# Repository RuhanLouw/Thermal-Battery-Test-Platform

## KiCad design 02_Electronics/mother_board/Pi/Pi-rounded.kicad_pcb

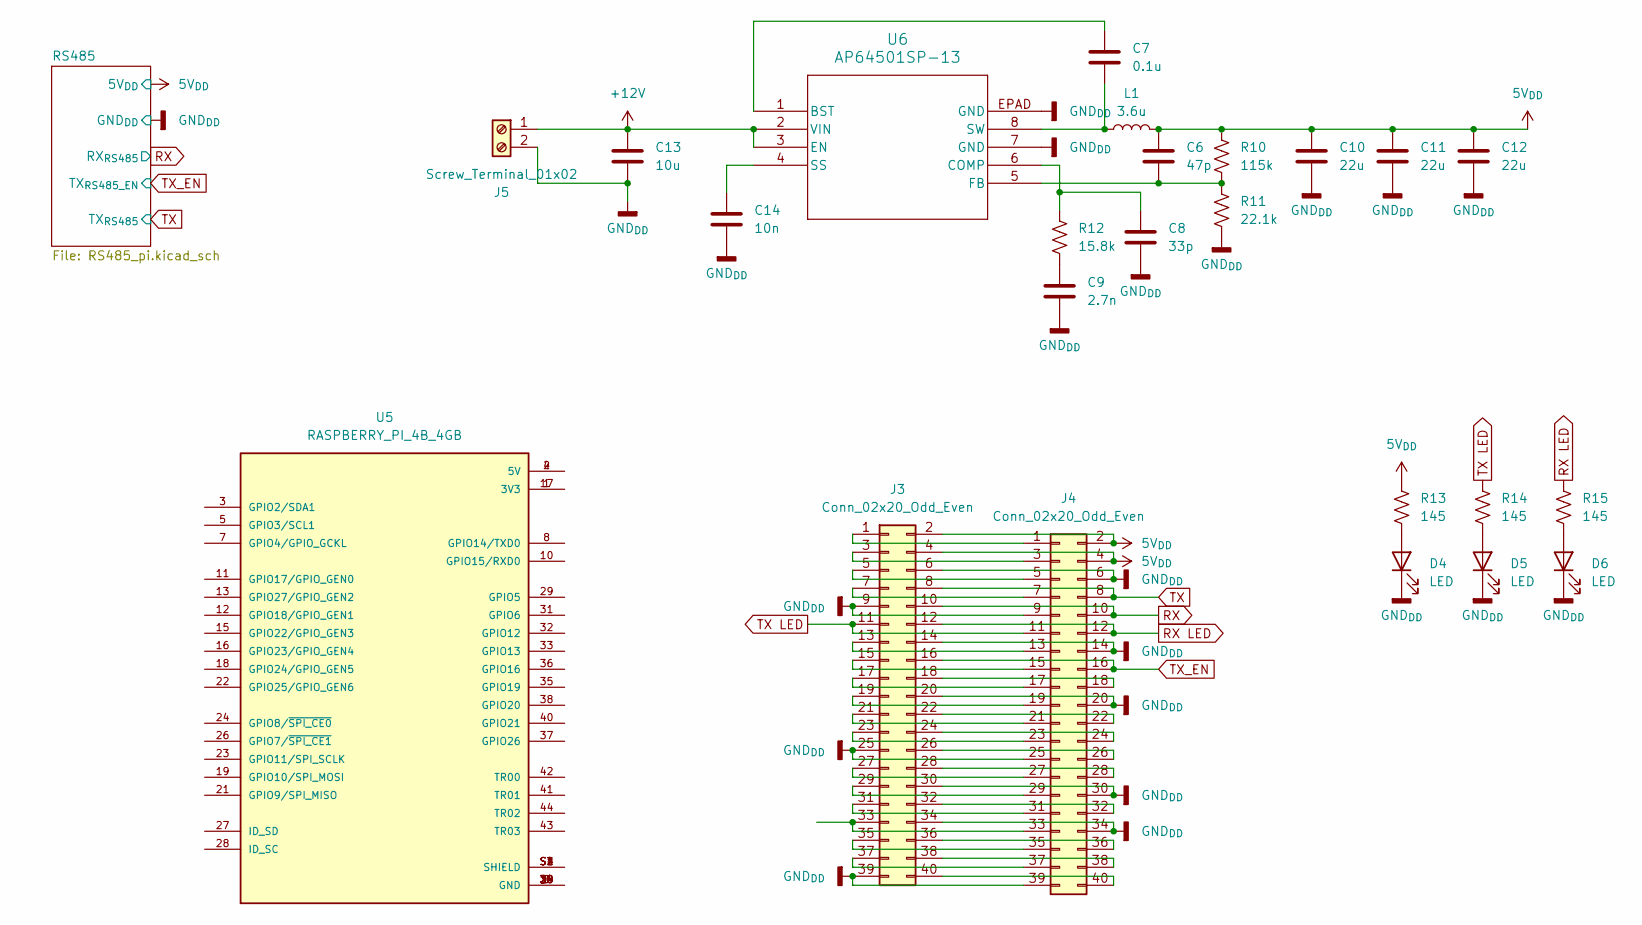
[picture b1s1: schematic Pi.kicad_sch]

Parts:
C6: 47p; C_0603_1608Metric
C7: 0.1u; C_0603_1608Metric
C8: 33p; C_0603_1608Metric
C9: 2.7n; C_0603_1608Metric
C10, C11, C12: 22u; C_1206_3216Metric
C13: 10u; C_1206_3216Metric
C14: 10n; C_0603_1608Metric
D4, D5, D6: LED; LED_0805_2012Metric
J3: Conn_02x20_Odd_Even; IDC-Header_2x20_P2.54mm_Vertical
J4: Conn_02x20_Odd_Even; PinHeader_2x20_P2.54mm_Vertical
J5: Screw_Terminal_01x02; TE_282857-2_screw
L1: 3.6u; WE-PDF_1064
R10: 115k; R_0603_1608Metric
R11: 22.1k; R_0603_1608Metric
R12: 15.8k; R_0603_1608Metric
R13, R14, R15: 145; R_0603_1608Metric
U5: RASPBERRY_PI_4B_4GB; MODULE_RASPBERRY_PI_4B_4GB; PARTREV 4
U6: AP64501SP-13

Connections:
5V_{DD}: C6.1, C10.1, C11.1, C12.1, J3.2, J3.4, J4.2, J4.4, L1.2, R10.1, R13.1; also elsewhere on the board
+12V: C13.1, J5.1, U6.2 (VIN), U6.3 (EN)
GND_{DD}: C8.2, C9.2, C10.2, C11.2, C12.2, C13.2, C14.2, D4.1 (K), D5.1 (K), D6.1 (K), J3.6, J3.9, J3.14, J3.20, J3.25, J3.30, J3.34, J3.39, J4.6, J4.9, J4.14, J4.20, J4.25, J4.30, J4.34, J4.39, J5.2, R11.2, U6.7 (GND), U6.EPAD (GND); also elsewhere on the board
unnamed: C9.1, R12.2
unnamed: D4.2 (A), R13.2
unnamed: D5.2 (A), R14.2
unnamed: D6.2 (A), R15.2
unnamed: J3.1, J4.1
unnamed: J3.3, J4.3
unnamed: J3.5, J4.5
unnamed: J3.7, J4.7
unnamed: J3.13, J4.13
unnamed: J3.15, J4.15
unnamed: J3.17, J4.17
unnamed: J3.18, J4.18
unnamed: J3.19, J4.19
unnamed: J3.21, J4.21
unnamed: J3.22, J4.22
unnamed: J3.23, J4.23
unnamed: J3.24, J4.24
unnamed: J3.26, J4.26
unnamed: J3.27, J4.27
unnamed: J3.28, J4.28
unnamed: J3.29, J4.29
unnamed: J3.31, J4.31
unnamed: J3.32, J4.32
unnamed: J3.33, J4.33
unnamed: J3.35, J4.35
unnamed: J3.36, J4.36
unnamed: J3.37, J4.37
unnamed: J3.38, J4.38
unnamed: J3.40, J4.40
unnamed: U5.1 (3V3), U5.17 (3V3)
unnamed: U5.2 (5V), U5.4 (5V)
unnamed: U5.6 (GND), U5.9 (GND), U5.14 (GND), U5.20 (GND), U5.25 (GND), U5.30 (GND), U5.34 (GND), U5.39 (GND)
unnamed: U5.S1 (SHIELD), U5.S2 (SHIELD), U5.S3 (SHIELD), U5.S4 (SHIELD)
unnamed: C7.1, U6.1 (BST)
unnamed: C8.1, R12.1, U6.6 (COMP)
unnamed: C6.2, R10.2, R11.1, U6.5 (FB)
unnamed: C14.1, U6.4 (SS)
unnamed: C7.2, L1.1, U6.8 (SW)
RX: J3.10, J4.10; also elsewhere on the board
RX LED: J3.12, J4.12, R15.1
TX: J3.8, J4.8; also elsewhere on the board
TX LED: J3.11, J4.11, R14.1
TX_EN: J3.16, J4.16; also elsewhere on the board

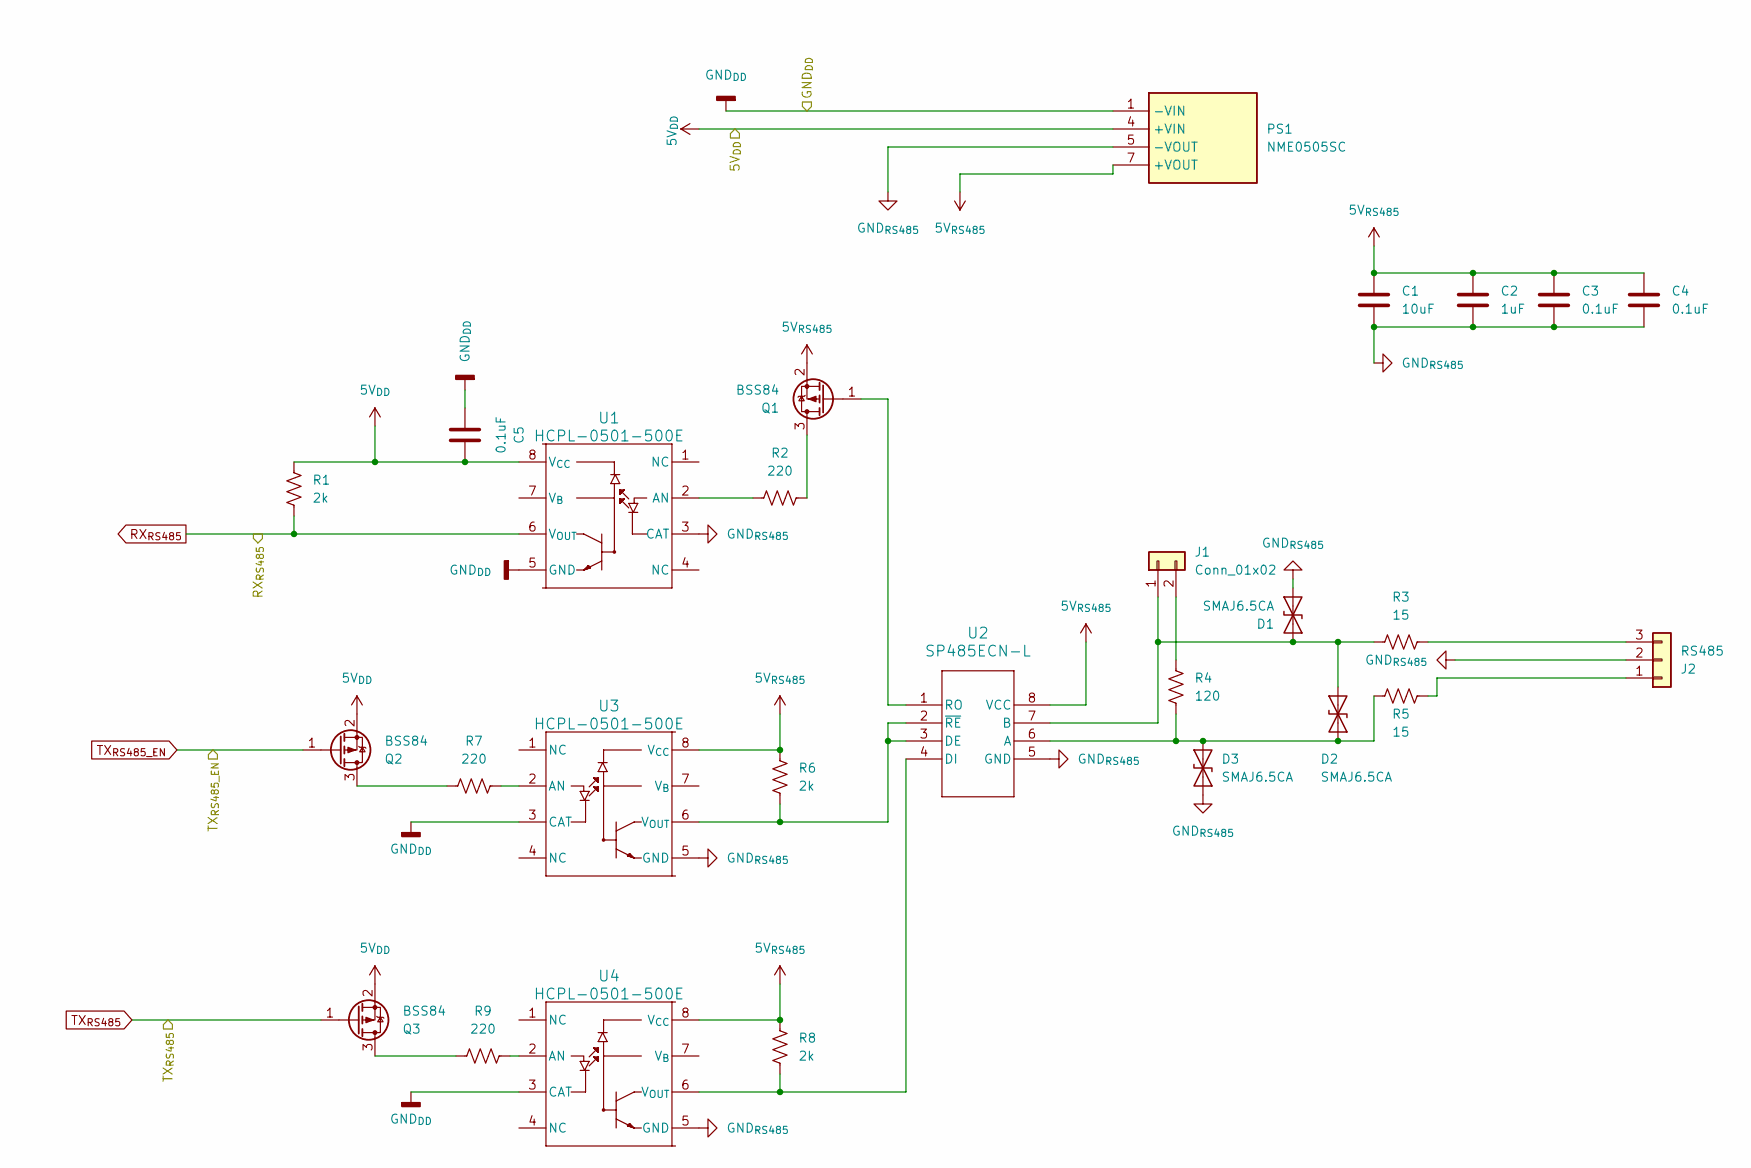
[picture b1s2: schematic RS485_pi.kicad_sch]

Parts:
C1: 10uF; C_0805_2012Metric
C2: 1uF; C_0603_1608Metric
C3, C4, C5: 0.1uF; C_0603_1608Metric
D1, D2, D3: SMAJ6.5CA; D_SMA
J1: Conn_01x02; PinHeader_1x02_P2.54mm_Vertical
J2: RS485; TE_282857-3_screw
PS1: NME0505SC; Mouser Part Number 580-NME0505SC
Q1, Q2, Q3: BSS84; SOT-23
R1, R6, R8: 2k; R_0603_1608Metric
R2, R7, R9: 220; R_0603_1608Metric
R3, R5: 15; R_1206_3216Metric
R4: 120; R_0603_1608Metric
U1, U3, U4: HCPL-0501-500E; SO8_HCPL-0501-500_BRA
U2: SP485ECN-L; NSOIC-8

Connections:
5V_{DD}: C5.2, PS1.4 (+VIN), Q2.2 (S), Q3.2 (S), R1.2, U1.8 (V_{CC}); also elsewhere on the board
5V_{RS485}: C1.1, C2.1, C3.1, C4.1, PS1.7 (+VOUT), Q1.2 (S), R6.2, R8.2, U2.8 (VCC), U3.8 (V_{CC}), U4.8 (V_{CC})
GND_{DD}: C5.1, PS1.1 (-VIN), U1.5 (GND), U3.3 (CAT), U4.3 (CAT); also elsewhere on the board
GND_{RS485}: C1.2, C2.2, C3.2, C4.2, D1.1 (A1), D3.1 (A1), J2.2, PS1.5 (-VOUT), U1.3 (CAT), U2.5 (GND), U3.5 (GND), U4.5 (GND)
unnamed: D1.2 (A2), D2.1 (A1), J1.1, R3.1, U2.7 (B)
unnamed: D2.2 (A2), D3.2 (A2), R4.2, R5.1, U2.6 (A)
unnamed: J1.2, R4.1
unnamed: J2.1, R5.2
unnamed: J2.3, R3.2
unnamed: Q1.3 (D), R2.1
unnamed: Q1.1 (G), U2.1 (RO)
unnamed: Q2.3 (D), R7.1
unnamed: Q3.3 (D), R9.1
unnamed: R2.2, U1.2 (AN)
unnamed: R6.1, U2.2 (~RE), U2.3 (DE), U3.6 (V_{OUT})
unnamed: R8.1, U2.4 (DI), U4.6 (V_{OUT})
unnamed: R7.2, U3.2 (AN)
unnamed: R9.2, U4.2 (AN)
RX: R1.1, U1.6 (V_{OUT}); also elsewhere on the board
TX: Q3.1 (G); also elsewhere on the board
TX_EN: Q2.1 (G); also elsewhere on the board

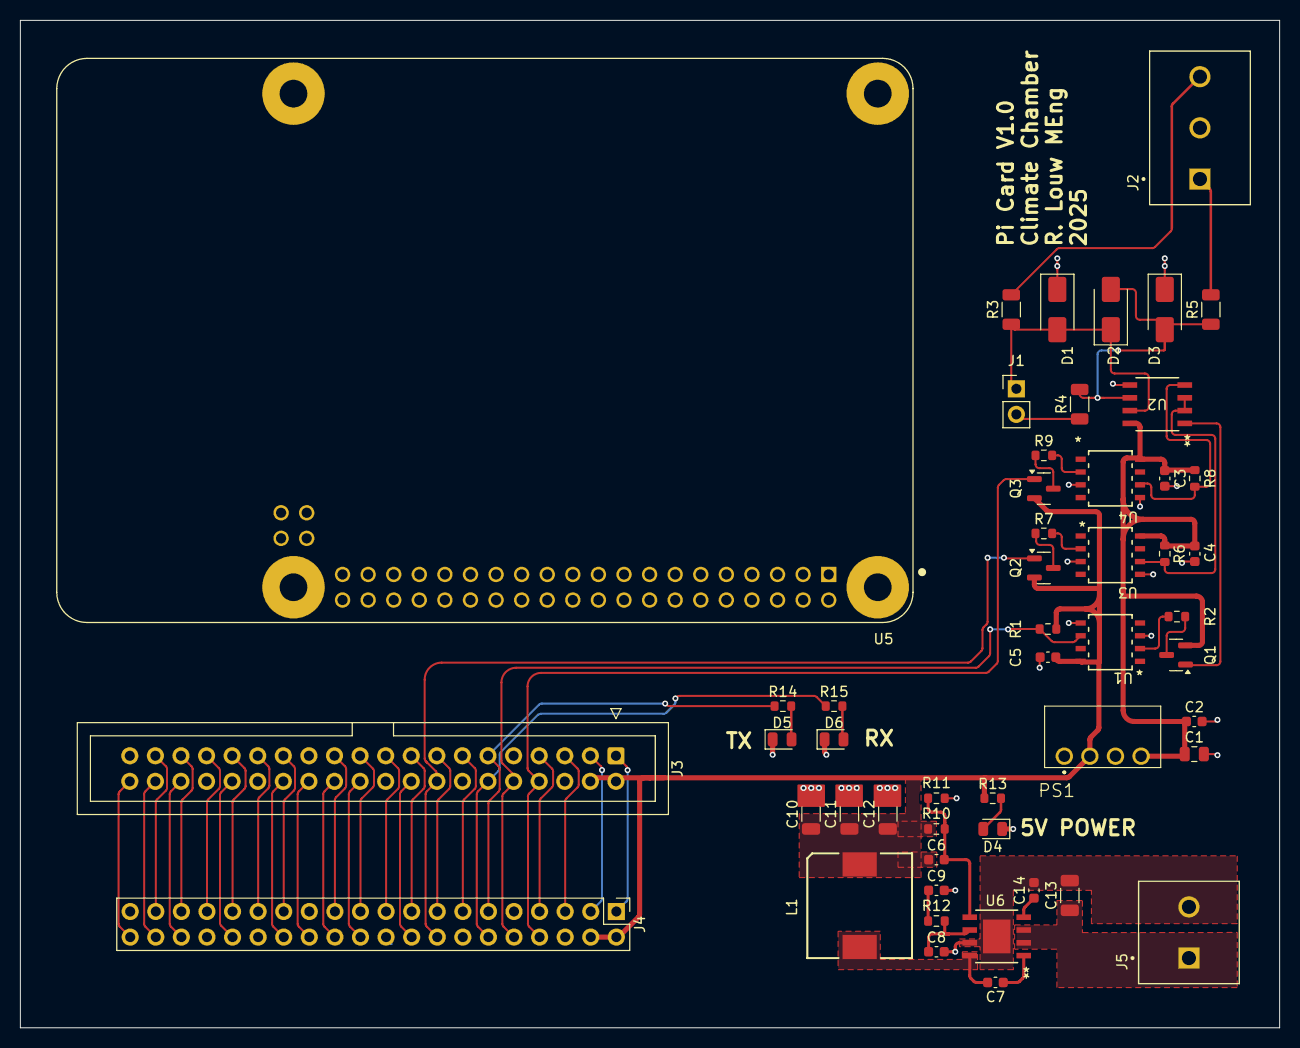
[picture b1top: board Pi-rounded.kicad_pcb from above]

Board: 2 copper layers, 125.0 x 100.0 mm, 51 parts (0 on the bottom side), 62 nets.

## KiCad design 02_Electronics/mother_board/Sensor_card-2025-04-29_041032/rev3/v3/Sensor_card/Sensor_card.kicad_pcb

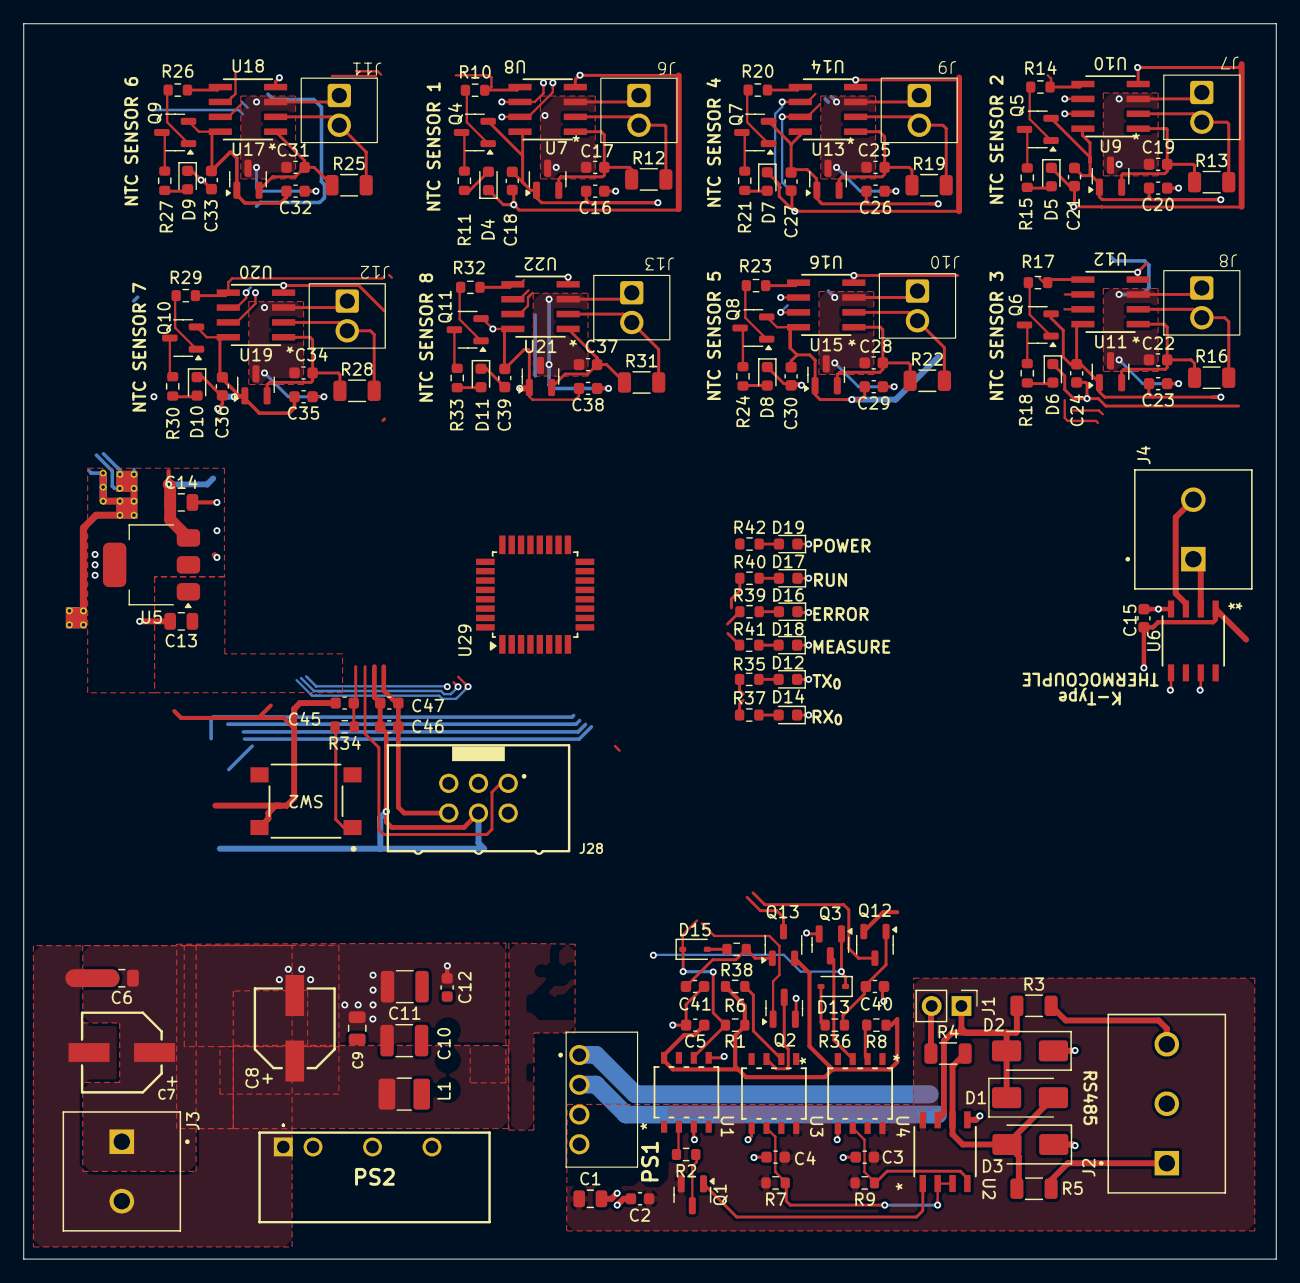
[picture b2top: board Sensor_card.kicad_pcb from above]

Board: 2 copper layers, 107.0 x 105.5 mm, 162 parts (0 on the bottom side), 107 nets.

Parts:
C1, C6, C8, C13, C14: 10uF; C_0805_2012Metric
C2: 1uF; C_0603_1608Metric
C3, C4, C5, C12, C15, C17, C18, C19, C21, C22, C24, C25, C27, C28, C30, C31, C33, C34, C36, C37, C39, C40, C41, C45: 0.1uF; C_0603_1608Metric
C7: 47uF; WCAP-ASLI_6.3X5.5_DXL_47uF
C9: 100uF; WCAP-ASLI_6.3X7.7_DXL_
C10, C11: 22uF; C_1210_3225Metric
C16, C20, C23, C26, C29, C32, C35, C38: 2.2uF; C_0603_1608Metric
C46: 1u; C_0603_1608Metric
C47: 10n; C_0603_1608Metric
D1, D2, D3: SMAJ5.0CA; D_SMA
D4, D5, D6, D7, D8, D9, D10, D11, D12, D14, D16, D17, D18, D19: LED; LED_0603_1608Metric
D13, D15: SD101CWS-TP; D_SOD-323
J1: Conn_01x02; PinHeader_1x02_P2.54mm_Vertical
J2: RS485; TE_282857-3_screw
J3, J4: Screw_Terminal_01x02; TE_282857-2_screw
J6, J7, J8, J9, J10, J11, J12, J13: Screw_Terminal_01x02; TERM BLOCK 2P HORIZON 2.54MM PCB
J28: Conn_02x03_Top_Bottom; 61200621621
L1: 4.7uH; L_1210_3225Metric_Pad1.42x2.65mm_HandSolder_cad
NT4: NetTie_3; NetTie-3_THT_Pad0.3mm
NT5, NT6, NT7: NetTie_4; NetTie-4_THT_Pad0.3mm
PS1: NME0505SC
PS2: NMG1205SC
Q1, Q2, Q3: BSS84; SOT-23
Q4, Q5, Q6, Q7, Q8, Q9, Q10, Q11: PNP; SOT-23-3 MMBT3906
Q12, Q13: MMBT2907A-TP; SOT-23-3 MMBT2907A
R1, R7, R9: 1k; R_0603_1608Metric
R2, R6, R8: 120; R_0603_1608Metric
R3, R4, R5: 120; R_1206_3216Metric
R10, R14, R17, R20, R23, R26, R29, R32, R36, R38: 10k; R_0603_1608Metric
R11, R15, R18, R21, R24, R27, R30, R33, R35, R37, R39, R40, R41, R42: 300; R_0603_1608Metric
R12, R13, R16, R19, R22, R25, R28, R31: 10k; R_1206_3216Metric
R34: 330; R_0603_1608Metric
SW2: SW_Push; SWITCH_43SMTR92LFS
U1, U3, U4: HCPL-0501-500E; SO8_HCPL-0501-500_BRA
U2: SP485ECN-L; NSOIC-8
U5: MIC5239-3.3YS; SOT-223-3_TabPin2
U6: MAX31855KASA+T; 21-0041B_8_MXM
U7, U9, U11, U13, U15, U17, U19, U21: REF3330AIDBZR; SOT-23
U8, U10, U12, U14, U16, U18, U20, U22: MCP3201; SOIC8-N_MC_MCH
U29: AVR128DA32x-xPT; TQFP-32_7x7mm_P0.8mm

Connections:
3.3V_{DD}: C5.2, C14.1, C15.2, C16.2, C18.2, C20.2, C21.2, C23.2, C24.2, C26.2, C27.2, C29.2, C30.2, C32.2, C33.2, C35.2, C36.2, C38.2, C39.2, C45.1, C46.1, C47.1, J28.4, Q4.3 (E), Q5.3 (E), Q6.3 (E), Q7.3 (E), Q8.3 (E), Q9.3 (E), Q10.3 (E), Q11.3 (E), Q12.1 (E), Q13.1 (E), R1.2, R6.1, R8.1, R42.1, SW2.2, U1.8 (V_{CC}), U5.3 (VO), U6.4 (VCC), U7.1 (IN), U8.8 (Vdd), U9.1 (IN), U10.8 (Vdd), U11.1 (IN), U12.8 (Vdd), U13.1 (IN), U14.8 (Vdd), U15.1 (IN), U16.8 (Vdd), U17.1 (IN), U18.8 (Vdd), U19.1 (IN), U20.8 (Vdd), U21.1 (IN), U22.8 (Vdd), U29.28 (VDD)
5V_{DD_unfiltered}: C8.1, C9.1, L1.2, PS2.6 (+VOUT)
5V_{DD}: C10.1, C11.1, C12.1, C13.1, L1.1, PS1.4 (+VIN), U5.1 (VI)
5V_{RS485}: C1.1, C2.1, C3.1, C4.1, PS1.7 (+VOUT), Q1.2 (S), R7.2, R9.2, U2.8 (VCC), U3.8 (V_{CC}), U4.8 (V_{CC})
12V_{CC}: C6.1, C7.1, J3.1, PS2.1 (_+VIN)
ERROR: R39.1, U29.21 (XTAL32K2/PF1)
GNDA_{NTC1}: C16.1, C17.1, J6.2, NT6.2, U7.3 (GND), U8.3 (IN-)
GNDA_{NTC2}: C19.1, C20.1, J7.2, NT6.4, U9.3 (GND), U10.3 (IN-)
GNDA_{NTC3}: C22.1, C23.1, J8.2, NT6.3, U11.3 (GND), U12.3 (IN-)
GNDA_{NTC4}: C25.1, C26.1, J9.2, NT4.2, U13.3 (GND), U14.3 (IN-)
GNDA_{NTC5}: C28.1, C29.1, J10.2, NT4.3, U15.3 (GND), U16.3 (IN-)
GNDA_{NTC6}: C31.1, C32.1, J11.2, NT5.4, U17.3 (GND), U18.3 (IN-)
GNDA_{NTC7}: C34.1, C35.1, J12.2, NT5.2, U19.3 (GND), U20.3 (IN-)
GNDA_{NTC8}: C37.1, C38.1, J13.2, NT5.3, U21.3 (GND), U22.3 (IN-)
GND_{CC}: C6.2, C7.2, J3.2, PS2.2 (-VIN)
GND_{DD}: C5.1, C8.2, C9.2, C10.2, C11.2, C12.2, C13.2, C14.2, C15.1, C18.1, C21.1, C24.1, C27.1, C30.1, C33.1, C36.1, C39.1, C40.1, C41.1, C46.2, C47.2, D4.1 (K), D5.1 (K), D6.1 (K), D7.1 (K), D8.1 (K), D9.1 (K), D10.1 (K), D11.1 (K), D12.1 (K), D14.1 (K), D16.1 (K), D17.1 (K), D18.1 (K), D19.1 (K), J28.6, NT7.1, PS1.1 (-VIN), PS2.4 (-VOUT), Q2.2 (S), Q3.2 (S), U1.5 (GND), U5.2 (GND), U6.1 (GND), U8.4 (Vss), U10.4 (Vss), U12.4 (Vss), U14.4 (Vss), U16.4 (Vss), U18.4 (Vss), U20.4 (Vss), U22.4 (Vss), U29.19 (GND), U29.29 (GND)
GND_{RS485}: C1.2, C2.2, C3.2, C4.2, D1.1 (A1), D3.1 (A1), J2.2, PS1.5 (-VOUT), U1.3 (CAT), U2.5 (GND), U3.5 (GND), U4.5 (GND)
MCU_RESET: C45.2, R34.1, U29.26 (~RESET/PF6)
MCU_UDPI: J28.1, U29.27 (UPDI)
MEAS: R41.1, U29.20 (XTAL32K1/PF0)
NTC1_~CS: R10.1, U8.5 (~CS/SHDN), U29.16 (PD6)
NTC2_~CS: R14.1, U10.5 (~CS/SHDN), U29.15 (PD5)
NTC3_~CS: R17.1, U12.5 (~CS/SHDN), U29.14 (PD4)
NTC4_~CS: R20.1, U14.5 (~CS/SHDN), U29.13 (PD3)
NTC5_~CS: R23.1, U16.5 (~CS/SHDN), U29.12 (PD2)
NTC6_~CS: R26.1, U18.5 (~CS/SHDN), U29.11 (PD1)
NTC7_~CS: R29.1, U20.5 (~CS/SHDN), U29.10 (PD0)
NTC8_~CS: R32.1, U22.5 (~CS/SHDN), U29.9 (PC3)
unnamed: D1.2 (A2), D2.1 (A1), J1.1, R3.1, U2.7 (B)
unnamed: D2.2 (A2), D3.2 (A2), R4.2, R5.1, U2.6 (A)
unnamed: D4.2 (A), R11.1
unnamed: D5.2 (A), R15.1
unnamed: D6.2 (A), R18.1
unnamed: D7.2 (A), R21.1
unnamed: D8.2 (A), R24.1
unnamed: D9.2 (A), R27.1
unnamed: D10.2 (A), R30.1
unnamed: D11.2 (A), R33.1
unnamed: D12.2 (A), R35.2
unnamed: D13.2 (A), R36.1
unnamed: D14.2 (A), R37.2
unnamed: D15.2 (A), R38.1
unnamed: D16.2 (A), R39.2
unnamed: D17.2 (A), R40.2
unnamed: D18.2 (A), R41.2
unnamed: D19.2 (A), R42.2
unnamed: J1.2, R4.1
unnamed: J2.1, R5.2
unnamed: J2.3, R3.2
unnamed: J4.1, U6.2 (T-)
unnamed: J4.2, U6.3 (T+)
unnamed: J6.1, R12.2, U8.2 (IN+)
unnamed: J7.1, R13.2, U10.2 (IN+)
unnamed: J8.1, R16.2, U12.2 (IN+)
unnamed: J9.1, R19.2, U14.2 (IN+)
unnamed: J10.1, R22.2, U16.2 (IN+)
unnamed: J11.1, R25.2, U18.2 (IN+)
unnamed: J12.1, R28.2, U20.2 (IN+)
unnamed: J13.1, R31.2, U22.2 (IN+)
unnamed: NT4.1, NT7.4
unnamed: NT5.1, NT7.3
unnamed: NT6.1, NT7.2
unnamed: Q1.3 (D), R2.1
unnamed: Q1.1 (G), U2.1 (RO)
unnamed: Q2.3 (D), U3.3 (CAT)
unnamed: Q3.3 (D), U4.3 (CAT)
unnamed: Q4.2 (B), R10.2
unnamed: Q4.1 (C), R11.2
unnamed: Q5.2 (B), R14.2
unnamed: Q5.1 (C), R15.2
unnamed: Q6.2 (B), R17.2
unnamed: Q6.1 (C), R18.2
unnamed: Q7.2 (B), R20.2
unnamed: Q7.1 (C), R21.2
unnamed: Q8.2 (B), R23.2
unnamed: Q8.1 (C), R24.2
unnamed: Q9.2 (B), R26.2
unnamed: Q9.1 (C), R27.2
unnamed: Q10.2 (B), R29.2
unnamed: Q10.1 (C), R30.2
unnamed: Q11.2 (B), R32.2
unnamed: Q11.1 (C), R33.2
unnamed: C40.2, Q12.2 (B), R36.2
unnamed: Q12.3 (C), R35.1
unnamed: C41.2, Q13.2 (B), R38.2
unnamed: Q13.3 (C), R37.1
unnamed: R34.2, SW2.1
unnamed: R2.2, U1.2 (AN)
unnamed: R7.1, U2.2 (~RE), U2.3 (DE), U3.6 (V_{OUT})
unnamed: R9.1, U2.4 (DI), U4.6 (V_{OUT})
unnamed: R6.2, U3.2 (AN)
unnamed: R8.2, U4.2 (AN)
unnamed: C17.2, R12.1, U7.2 (OUT), U8.1 (Vref)
unnamed: C19.2, R13.1, U9.2 (OUT), U10.1 (Vref)
unnamed: C22.2, R16.1, U11.2 (OUT), U12.1 (Vref)
unnamed: C25.2, R19.1, U13.2 (OUT), U14.1 (Vref)
unnamed: C28.2, R22.1, U15.2 (OUT), U16.1 (Vref)
unnamed: C31.2, R25.1, U17.2 (OUT), U18.1 (Vref)
unnamed: C34.2, R28.1, U19.2 (OUT), U20.1 (Vref)
unnamed: C37.2, R31.1, U21.2 (OUT), U22.1 (Vref)
RUN: R40.1, U29.22 (PF2)
RX_{RS485}: D15.1 (K), R1.1, U1.6 (V_{OUT}), U29.3 (PA5)
SPI0_MISO: U6.7 (SO), U8.6 (Dout), U10.6 (Dout), U12.6 (Dout), U14.6 (Dout), U16.6 (Dout), U18.6 (Dout), U20.6 (Dout), U22.6 (Dout), U29.7 (PC1)
SPI0_SCK: U6.5 (SCK), U8.7 (CLK), U10.7 (CLK), U12.7 (CLK), U14.7 (CLK), U16.7 (CLK), U18.7 (CLK), U20.7 (CLK), U22.7 (CLK), U29.8 (PC2)
TX_{RS485_EN}: Q2.1 (G), U29.5 (PA7)
TX_{RS485}: D13.1 (K), Q3.1 (G), U29.2 (PA4)
Therm_~CS: U6.6 (*CS), U29.17 (VREFA/PD7)

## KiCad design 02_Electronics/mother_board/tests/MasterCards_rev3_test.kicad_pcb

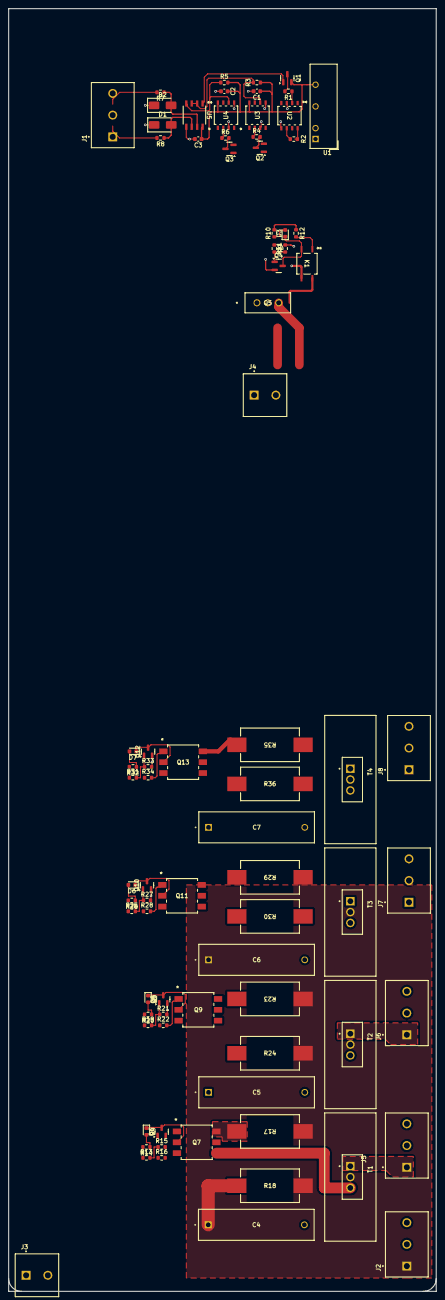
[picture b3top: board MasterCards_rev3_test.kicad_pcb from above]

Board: 2 copper layers, 100.0 x 300.0 mm, 81 parts (0 on the bottom side), 62 nets.

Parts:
C1: C10u; C_0603_1608Metric
C2: C1u; C_0603_1608Metric
C3: C0.1u; C_0603_1608Metric
C4, C5, C6, C7: 0.1uF; R474N310050A1KV057_KEM_01uF
D1, D2: SMAJ5.0CA; D_SMA
D3, D4, D5, D6, D7: LED; D_0603_1608Metric
J1: RS485; TE_282857-3_screw
J2: AC_in; TE_282857-3_screw
J3, J4: DC_sw; TE_282857-2_screw
J5, J6, J7, J8: AC_sw; TE_282857-3_screw
K1: APV1121S; SOP4PIN_PAN-M
Q1, Q2, Q3: BSS84; SOT-23
Q4, Q6, Q8, Q10, Q12: BSS138L; SOT-23
Q5: CSD18502KCS
Q7, Q9, Q11, Q13: MOC3063S-TA1; MOC306XS_LTO
R1: R215.5; R_0603_1608Metric
R2: R16.5k; R_0603_1608Metric
R3, R5: R10k; R_0603_1608Metric
R4, R6: R109.3; R_0603_1608Metric
R7, R8: R15; R_0603_1608Metric
R9, R13, R19, R25, R31: 300; R_0603_1608Metric
R10, R14, R20, R26, R32: 142; R_0603_1608Metric
R11, R15, R21, R27, R33: 10k; R_0603_1608Metric
R12, R16, R22, R28, R34: 187; R_0603_1608Metric
R17, R23, R29, R35: 10K@5W; RES_SMF5_TYCO_TYC
R18, R24, R30, R36: R68; RES_SMF5_TYCO_TYC
T1, T2, T3, T4: BTA316-800E,127; TO254P1040X475X1935-3__U_heat
U1: TMA-0505S; Converter_DCDC_TRACO_TMA-05xxS_12xxS_Single_THT
U2, U3, U4: HCPL-0501-500E; SO8_HCPL-0501-500_BRA
U5: SP485ECN-L; NSOIC-8

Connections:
5V_{DD}: R10.2, R12.1, R14.2, R16.1, R20.2, R22.1, R26.2, R28.1, R32.2, R34.1
12V_{CC}: J3.1, J4.1
230AC: C6.1, J2.1, R17.1, R18.2, R23.1, R24.2, R29.1, R35.1, R36.2, T1.2, T2.2, T3.2, T4.2
Earth: J2.2, J5.2, J6.2, J7.2, J8.2
GND_{CC}: J3.2, K1.3, Q5.3 (S)
GND_{DD}: Q4.2 (S), Q6.2 (S), Q8.2 (S), Q10.2 (S), Q12.2 (S), R11.2, R15.2, R21.2, R27.2, R33.2, U1.2 (-Vin), U2.5 (GND), U3.3 (CAT), U4.3 (CAT)
GND_{RS485}: C1.2, C2.2, C3.2, D1.1 (A1), D2.1 (A1), J1.2, U1.4 (-Vout), U2.3 (CAT), U3.5 (GND), U4.5 (GND), U5.5 (GND)
NEUT: J2.3, J5.3, J6.3, J7.3, J8.3
unnamed: C4.1, R18.1
unnamed: C5.1, R24.1
unnamed: C6.2, R30.2
unnamed: C7.1, R36.1
unnamed: D1.2 (A2), R8.1, U5.6 (A)
unnamed: D2.2 (A2), R7.1, U5.7 (B)
unnamed: D3.2 (A), R10.1
unnamed: D3.1 (K), K1.2, Q4.3 (D)
unnamed: D4.2 (A), R14.1
unnamed: D4.1 (K), Q6.3 (D), Q7.2
unnamed: D5.2 (A), R20.1
unnamed: D5.1 (K), Q8.3 (D), Q9.2
unnamed: D6.2 (A), R26.1
unnamed: D6.1 (K), Q10.3 (D), Q11.2
unnamed: D7.2 (A), R32.1
unnamed: D7.1 (K), Q12.3 (D), Q13.2
unnamed: J1.1, R8.2
unnamed: J1.3, R7.2
unnamed: J4.2, Q5.1 (D)
unnamed: C4.2, J5.1, T1.1
unnamed: C5.2, J6.1, T2.1
unnamed: J7.1, R30.1, T3.1
unnamed: C7.2, J8.1, T4.1
unnamed: K1.1, R12.2
unnamed: Q1.3 (D), R1.2
unnamed: Q1.1 (G), U5.1 (RO)
unnamed: Q2.3 (D), R4.2
unnamed: Q3.3 (D), R6.2
unnamed: Q4.1 (G), R9.2, R11.1
unnamed: K1.4, Q5.2 (G)
unnamed: Q6.1 (G), R13.2, R15.1
unnamed: Q7.1, R16.2
unnamed: Q7.4, T1.3
unnamed: Q7.6, R17.2
unnamed: Q8.1 (G), R19.2, R21.1
unnamed: Q9.1, R22.2
unnamed: Q9.4, T2.3
unnamed: Q9.6, R23.2
unnamed: Q10.1 (G), R25.2, R27.1
unnamed: Q11.1, R28.2
unnamed: Q11.4, T3.3
unnamed: Q11.6, R29.2
unnamed: Q12.1 (G), R31.2, R33.1
unnamed: Q13.1, R34.2
unnamed: Q13.4, T4.3
unnamed: Q13.6, R35.2
unnamed: R1.1, U2.2 (AN)
unnamed: R4.1, U3.2 (AN)
unnamed: R3.1, U3.6 (V_{OUT}), U5.2 (~RE), U5.3 (DE)
unnamed: R6.1, U4.2 (AN)
unnamed: R5.1, U4.6 (V_{OUT}), U5.4 (DI)
RX_{RS485}: R2.1, U2.6 (V_{OUT})
V_{3.3V}: Q2.2 (S), Q3.2 (S), R2.2, U2.8 (V_{CC})
V_{RS485_5V}: C1.1, C2.1, C3.1, Q1.2 (S), R3.2, R5.2, U1.6 (+Vout), U3.8 (V_{CC}), U4.8 (V_{CC}), U5.8 (VCC)
